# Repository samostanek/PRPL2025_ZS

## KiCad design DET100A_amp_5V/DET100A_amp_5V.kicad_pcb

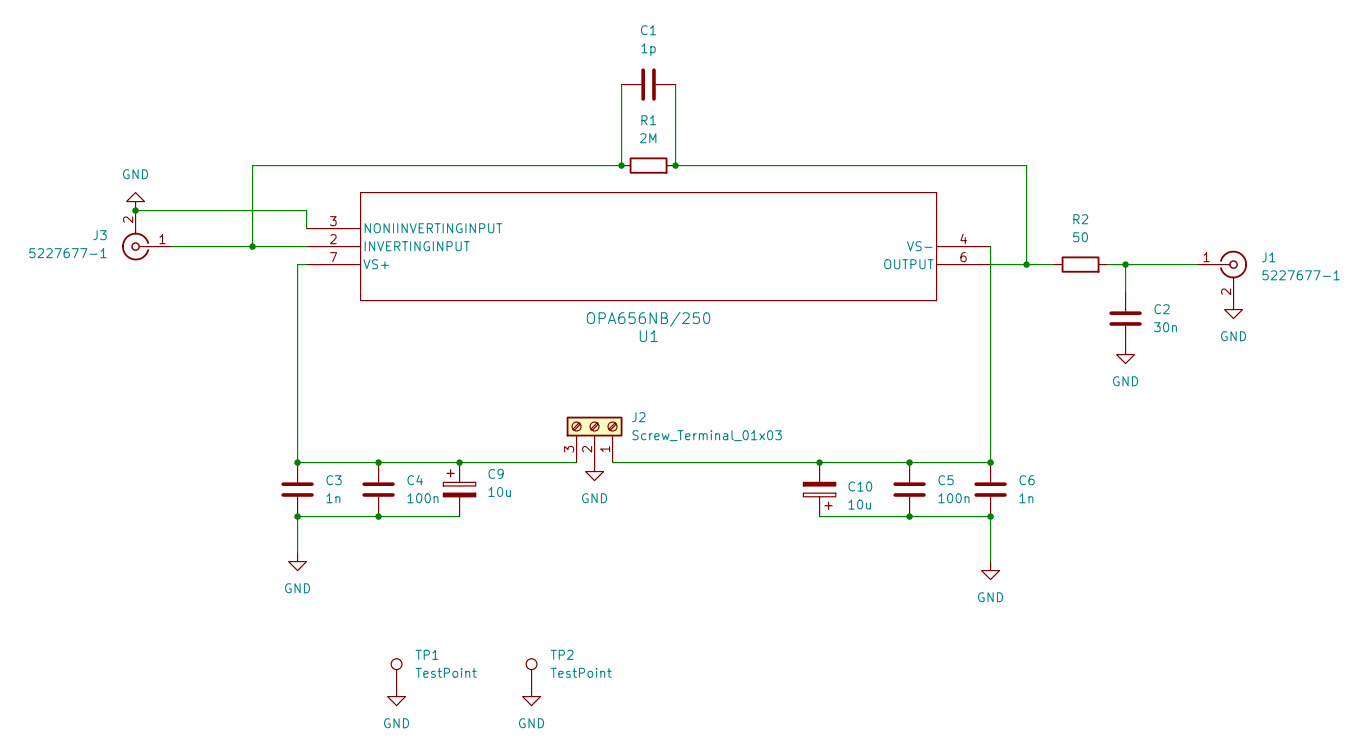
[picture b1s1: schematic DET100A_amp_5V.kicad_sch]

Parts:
C1: 1p; C_0603_1608Metric_Pad1.08x0.95mm_HandSolder
C2: 30n; C_0805_2012Metric_Pad1.18x1.45mm_HandSolder
C3, C6: 1n; C_0603_1608Metric_Pad1.08x0.95mm_HandSolder
C4, C5: 100n; C_0805_2012Metric_Pad1.18x1.45mm_HandSolder
C9, C10: 10u; C_0805_2012Metric_Pad1.18x1.45mm_HandSolder
J1, J3: 5227677-1; 52276771
J2: Screw_Terminal_01x03; TerminalBlock_TE_282834-3_1x03_P2.54mm_Horizontal
R1: 2M; R_0603_1608Metric_Pad0.98x0.95mm_HandSolder
R2: 50; R_0805_2012Metric_Pad1.20x1.40mm_HandSolder
TP1, TP2: TestPoint; TestPoint_THTPad_D2.0mm_Drill1.0mm
U1: OPA656NB/250; SOIC-8_5.3x5.3mm_P1.27mm

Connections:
GND: C2.1, C3.1, C4.1, C5.1, C6.1, C9.2, C10.1, J1.2 (Ext), J2.2, J3.2 (Ext), TP1.1 (1_1), TP2.1 (1_1), U1.3 (NONIINVERTINGINPUT)
unnamed: C2.2, J1.1 (In), R2.2
unnamed: C3.2, C4.2, C9.1, J2.3 (Pin_1), U1.7 (VS+)
unnamed: C5.2, C6.2, C10.2, J2.1 (Pin_3), U1.4 (VS-)
unnamed: C1.1, J3.1 (In), R1.1, U1.2 (INVERTINGINPUT)
unnamed: C1.2, R1.2, R2.1, U1.6 (OUTPUT)

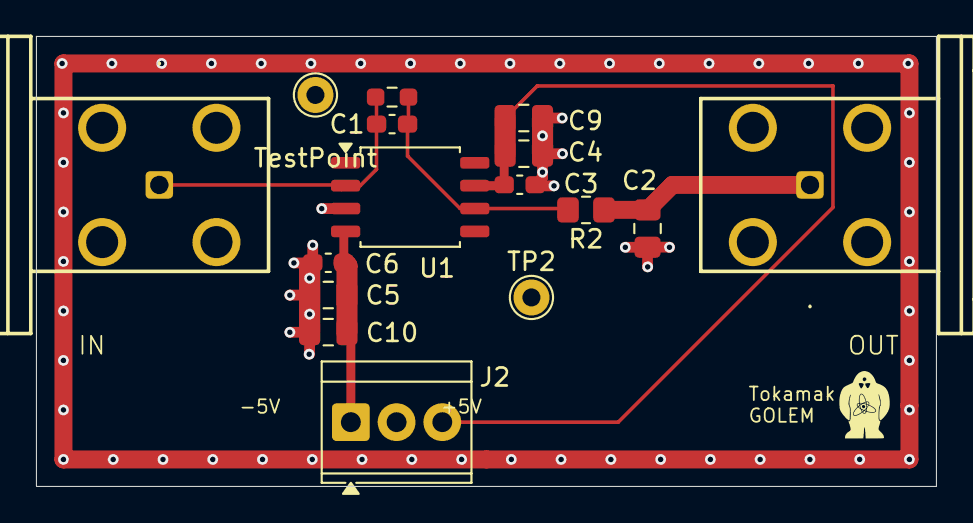
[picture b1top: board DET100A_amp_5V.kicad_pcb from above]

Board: 2 copper layers, 50.0 x 25.0 mm, 16 parts (0 on the bottom side), 6 nets.

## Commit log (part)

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2025-11-06 init
2025-11-11 feat: add spectrometer comparison
2025-11-11 feat: create golem_data_loader package
2025-11-11 feat: everything :D
2025-11-12 feat: update spectral lines
2025-11-13 feat: add QE computation
2025-11-16 feat: add QE data for X100 fast cameras
2025-11-16 feat: add fast cameras data to golem data loader
2025-11-16 feat: add `fast_camera_visualization.ipynb`
2025-12-03 refactor: use scipy for fast camera fft
2025-12-03 feat: update fast spectrometry for 8 detectors
2025-12-19 feat: add quantum efficiencies for H beta and H gamma lines
2025-12-22 Create docs for golem wiki WIP
2025-12-22 fix: adjust graphs to use plasma start end
2025-12-22 docs: add outline to logbook
2026-01-03 feat: add stacked graph
2026-01-04 Please check for errors :)
2026-01-10 Minor improvements
2026-01-18 feat: add amplitude comparison and conside QE in `fast_spectrometry_graphs.ipnb`
2026-01-18 feat: export quantum efficiency data
2026-01-18 fix: handle varying fast camera framerates properly
2026-01-20 dump
2026-02-19 misc
2026-02-23 docs: update wiki index
2026-02-23 docs: document the `quantum_efficiency.ipynb` notebook properly
2026-02-23 chore: remove useless files
2026-02-23 docs: update docs on `fast_camera_compare.py`
2026-02-23 chore: remove `fast_camera_visualization.ipynb`
2026-03-15 Add signal frequency analysis
2026-03-15 Fix spectra in golem_data_loader
2026-06-11 feat: add KiCad project for the amp
2026-06-21 feat: add KiCad project `DET100A_amp_12V`
2026-06-29 feat(PCB): add TPs for the 5V version
